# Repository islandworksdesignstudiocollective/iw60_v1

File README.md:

iw60_v1

****************************************************************************************

i was not impressed by the features, availability or price of other gh60 pcbs with o-ring compat so i made this

****************************************************************************************

-gh60 tray mount points

-all the baka nekos o-ring cutouts on edgecuts (afaik)

-alps+mx footprints

-onboad usb c, esd, h60 jst location yada yada

-routed to use no gnd plane cuz why not (a 2-sided fill zone has been drawn with isolation for the usb-c receptacle already, so you can choose to fill or remove it before making production files)

-duplex matrix cuz why not

-gondo reset circuit cuz why not

-bottom row is tsangan and 87u (so 7u wk/wkl or true hhkb or 87u wk with the 2 1us, as well as split space 3u) 

-does NOT support full right shift or ANSI bottom row 

-has accurately placed usb-c receptacle for gh60 standard. it is not lazily offset like most of the others i have seen, therefore i cannot confirm whether this will be well aligned with whatever pre-existing case that used a different gh60 compat pcb's 3d model to make their usb cutout

****************************************************************************************

as of right now, stm32g0b1cbt6 (and other stm mcus) seem to be in short supply, and other designers have reported issues with this mcu and qmk, so i have shelved this design. for that reason **this design has NOT been prototyped**. i don't have the energy right now to do a bom i will probably regret this in the future

the step file looks good to me. new versions of kicad are annoying to get the right thickness and export all the holes/components etc so if somethings missing its because i didn't notice :)

if you would like files for the same pcb with a different mcu you can check out iw60_v2 whenever i finish and publish that

****************************************************************************************

this is licensed under the Creative Commons Attribution Share-Alike 4.0 license, for the license's exact terms, see the LICENSE.md file

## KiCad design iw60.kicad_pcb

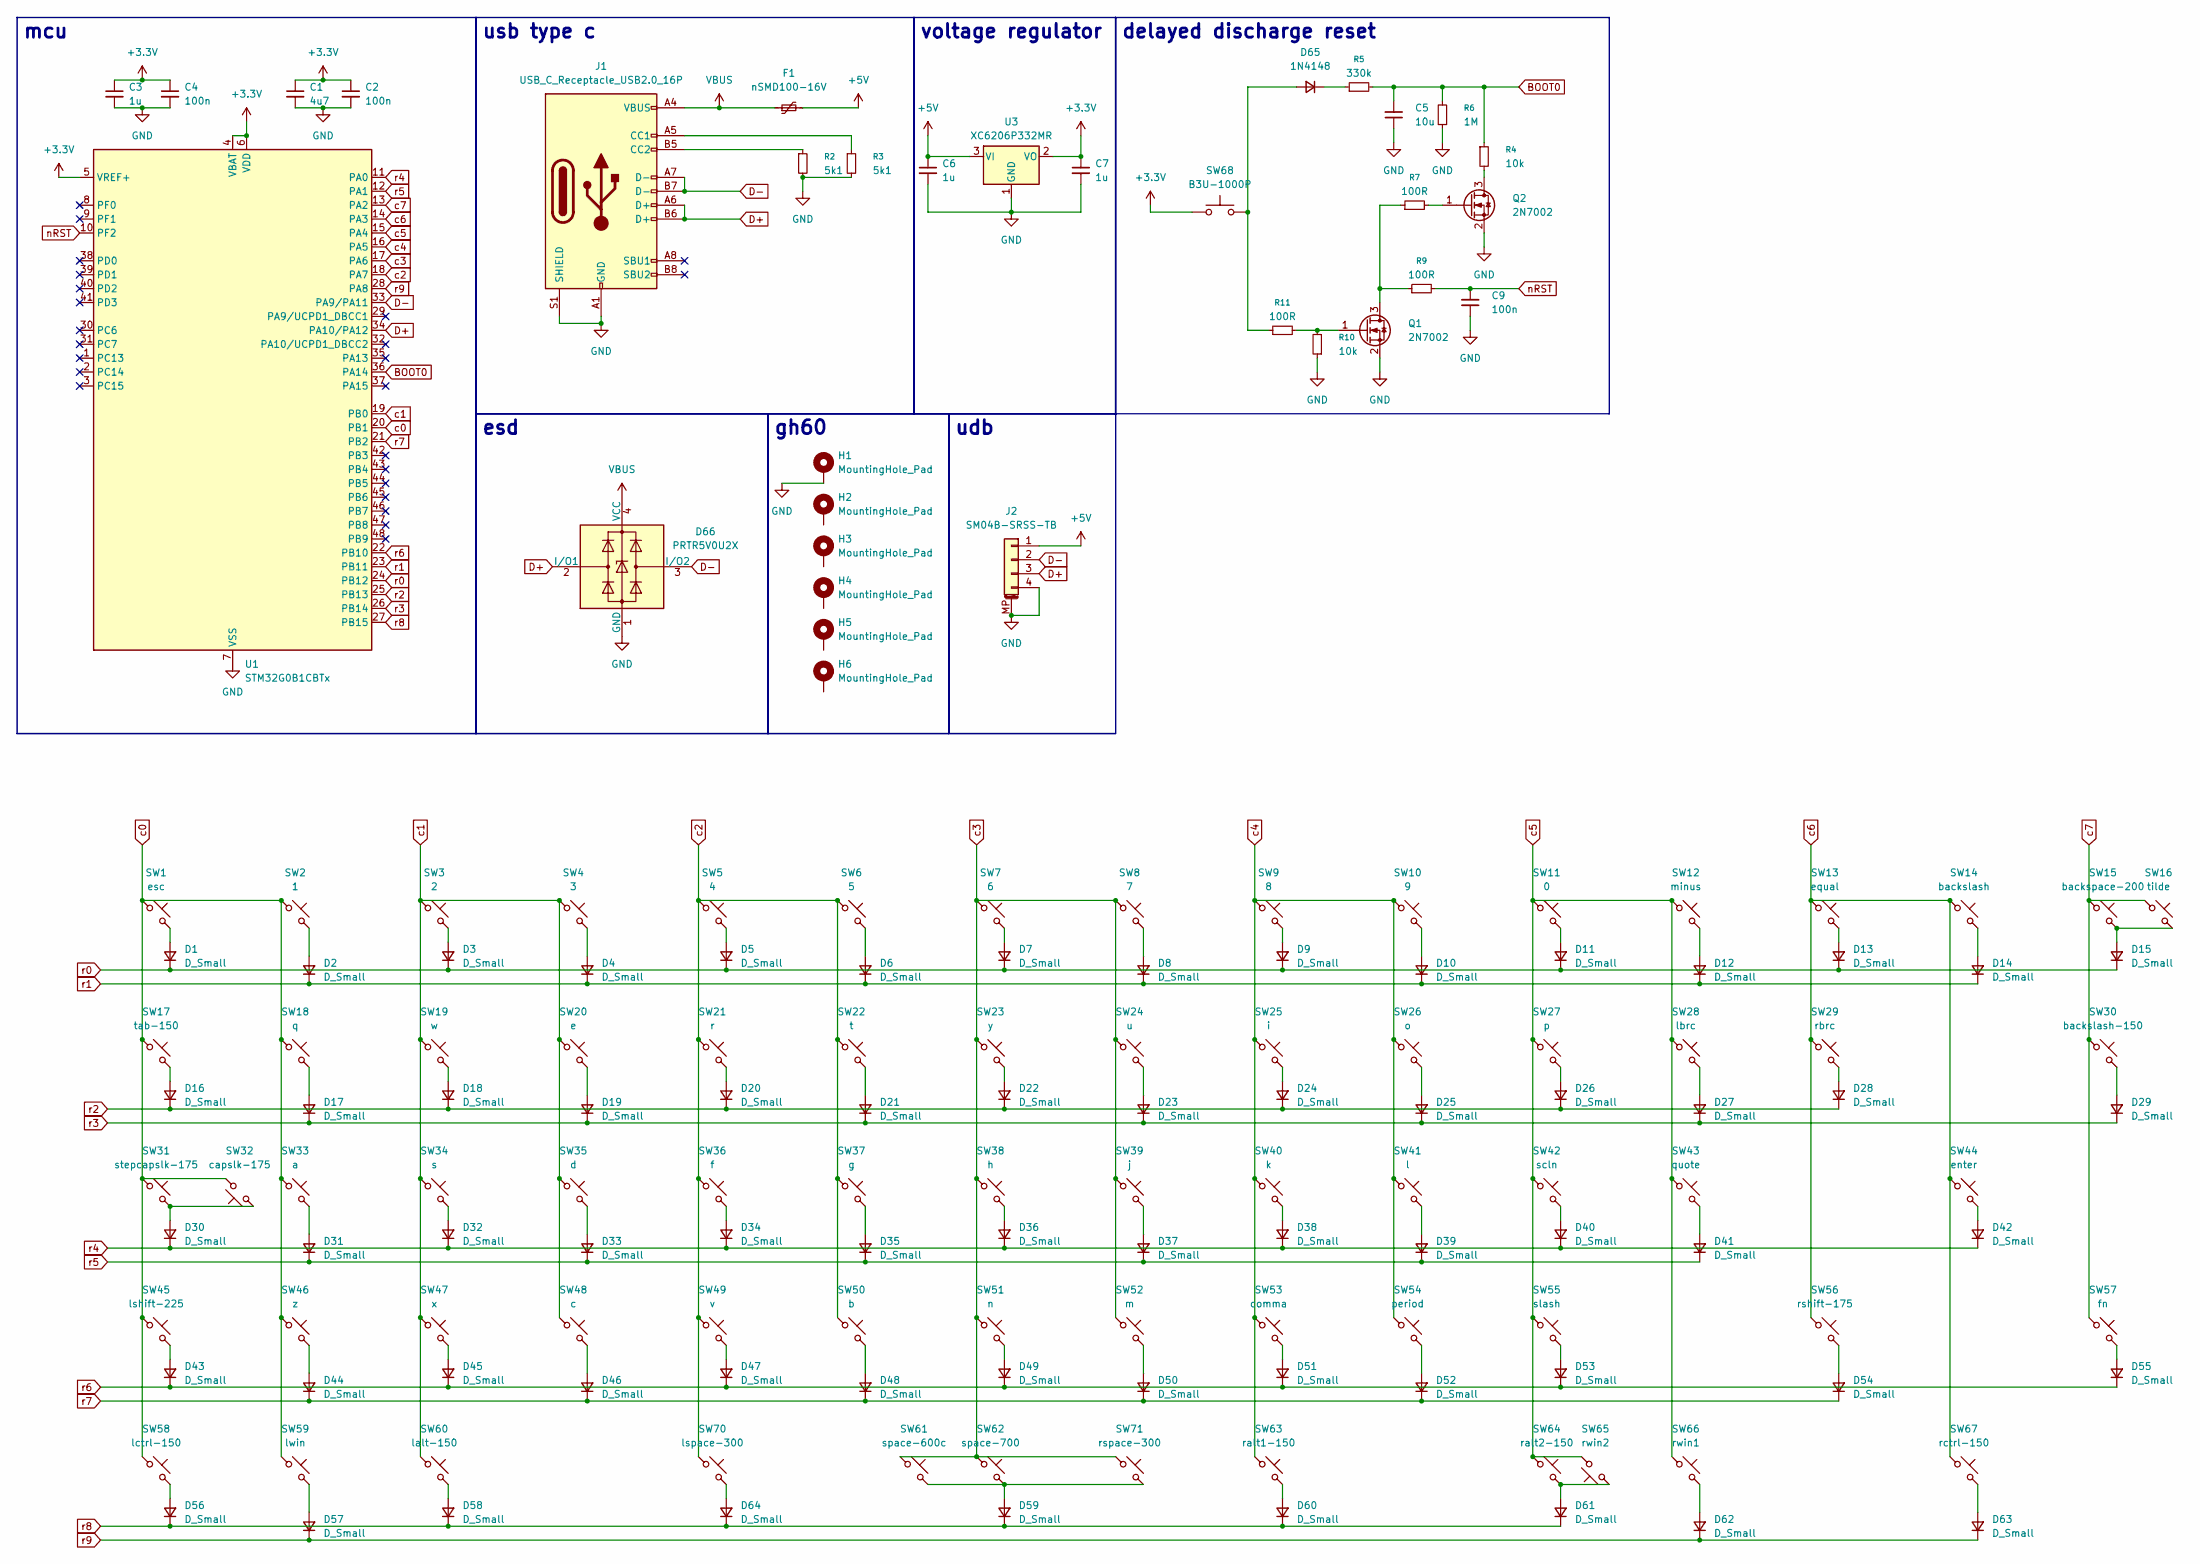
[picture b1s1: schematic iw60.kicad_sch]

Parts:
C1: 4u7; C_0402_1005Metric
C2, C4, C9: 100n; C_0402_1005Metric
C3, C6, C7: 1u; C_0402_1005Metric
C5: 10u; C_0402_1005Metric
D1, D2, D3, D4, D5, D6, D7, D8, D9, D10, D11, D12, D13, D14, D15, D16, D17, D18, D19, D20, D21, D22, D23, D24, D25, D26, D27, D28, D29, D30, D31, D32, D33, D34, D35, D36, D37, D38, D39, D40, D41, D42, D43, D44, D45, D46, D47, D48, D49, D50, D51, D52, D53, D54, D55, D56, D57, D58, D59, D60, D61, D62, D63, D64: D_Small; D_SOD-123
D65: 1N4148; D_SOD-123
D66: PRTR5V0U2X; SOT-143
F1: nSMD100-16V; Fuse_1206_3216Metric
H1: MountingHole_Pad; MountingHole_2.5mm_Pad_Via
H2, H3, H6: MountingHole_Pad; 5.5_5x2.5mm
H4, H5: MountingHole_Pad; 10x5_7x2.5mm
J1: USB_C_Receptacle_USB2.0_16P; USB_C_Receptacle_HRO_TYPE-C-31-M-12
J2: SM04B-SRSS-TB; JST_SH_SM04B-SRSS-TB_1x04-1MP_P1.00mm_Horizontal
Q1, Q2: 2N7002; SOT-23
R2, R3: 5k1; R_0402_1005Metric
R4, R10: 10k; R_0402_1005Metric
R5: 330k; R_0402_1005Metric
R6: 1M; R_0402_1005Metric
R7, R9, R11: 100R; R_0402_1005Metric
SW1: esc; MX-Alps-Hybrid-1U
SW2: 1; MX-Alps-Hybrid-1U-iw60-SW2
SW3: 2; MX-Alps-Hybrid-1U
SW4: 3; MX-Alps-Hybrid-1U
SW5: 4; MX-Alps-Hybrid-1U
SW6: 5; MX-Alps-Hybrid-1U
SW7: 6; MX-Alps-Hybrid-1U
SW8: 7; MX-Alps-Hybrid-1U
SW9: 8; MX-Alps-Hybrid-1U
SW10: 9; MX-Alps-Hybrid-1U
SW11: 0; MX-Alps-Hybrid-1U
SW12: minus; MX-Alps-Hybrid-1U
SW13: equal; MX-Alps-Hybrid-1U
SW14: backslash; MX-Alps-Hybrid-1U
SW15: backspace-200; MX-Alps-Hybrid-2U
SW16: tilde; MX-Alps-Hybrid-1U
SW17: tab-150; MX-Alps-Hybrid-1.5U
SW18: q; MX-Alps-Hybrid-1U
SW19: w; MX-Alps-Hybrid-1U
SW20: e; MX-Alps-Hybrid-1U
SW21: r; MX-Alps-Hybrid-1U
SW22: t; MX-Alps-Hybrid-1U
SW23: y; MX-Alps-Hybrid-1U
SW24: u; MX-Alps-Hybrid-1U
SW25: i; MX-Alps-Hybrid-1U
SW26: o; MX-Alps-Hybrid-1U
SW27: p; MX-Alps-Hybrid-1U
SW28: lbrc; MX-Alps-Hybrid-1U
SW29: rbrc; MX-Alps-Hybrid-1U
SW30: backslash-150; MX-Alps-Hybrid-1.5U
SW31: stepcapslk-175; MX-Alps-Hybrid-1.25U
SW32: capslk-175; MX-Alps-Hybrid-1.75U
SW33: a; MX-Alps-Hybrid-1U
SW34: s; MX-Alps-Hybrid-1U
SW35: d; MX-Alps-Hybrid-1U
SW36: f; MX-Alps-Hybrid-1U
SW37: g; MX-Alps-Hybrid-1U
SW38: h; MX-Alps-Hybrid-1U
SW39: j; MX-Alps-Hybrid-1U
SW40: k; MX-Alps-Hybrid-1U
SW41: l; MX-Alps-Hybrid-1U
SW42: scln; MX-Alps-Hybrid-1U
SW43: quote; MX-Alps-Hybrid-1U
SW44: enter; MX-Alps-Hybrid-2.25U
SW45: lshift-225; MX-Alps-Hybrid-2.25U
SW46: z; MX-Alps-Hybrid-1U
SW47: x; MX-Alps-Hybrid-1U
SW48: c; MX-Alps-Hybrid-1U
SW49: v; MX-Alps-Hybrid-1U
SW50: b; MX-Alps-Hybrid-1U
SW51: n; MX-Alps-Hybrid-1U
SW52: m; MX-Alps-Hybrid-1U
SW53: comma; MX-Alps-Hybrid-1U
SW54: period; MX-Alps-Hybrid-1U
SW55: slash; MX-Alps-Hybrid-1U
SW56: rshift-175; MX-Alps-Hybrid-1.75U
SW57: fn; MX-Alps-Hybrid-1U
SW58: lctrl-150; MX-Alps-Hybrid-1.5U
SW59: lwin; MX-Alps-Hybrid-1U
SW60: lalt-150; MX-Alps-Hybrid-1.5U
SW61: space-600c; MX-Alps-Hybrid-6U-ReversedStabilizers
SW62: space-700; MX-Alps-Hybrid-7U-ReversedStabilizers
SW63: ralt1-150; MX-Alps-Hybrid-1.5U
SW64: ralt2-150; MX-Alps-Hybrid-1.5U
SW65: rwin2; MX-Alps-Hybrid-1U
SW66: rwin1; MX-Alps-Hybrid-1U
SW67: rctrl-150; MX-Alps-Hybrid-1.5U
SW68: B3U-1000P; SW_SPST_B3U-1000P
SW70: lspace-300; MX-Alps-Hybrid-3U-ReversedStabilizers
SW71: rspace-300; MX-Alps-Hybrid-3U-ReversedStabilizers
U1: STM32G0B1CBTx; LQFP-48_7x7mm_P0.5mm
U3: XC6206P332MR; SOT-23-3

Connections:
+3.3V: C1.1, C2.1, C3.1, C4.1, C7.1, SW68.1, U1.4 (VBAT), U1.5 (VREF+), U1.6 (VDD), U3.2 (VO)
+5V: C6.1, F1.2, J2.1, U3.3 (VI)
BOOT0: C5.2, R4.1, R5.2, R6.2, U1.36 (PA14)
D+: D66.2 (I/O1), J1.A6 (D+), J1.B6 (D+), J2.3, U1.34 (PA10/PA12)
D-: D66.3 (I/O2), J1.A7 (D-), J1.B7 (D-), J2.2, U1.33 (PA9/PA11)
GND: C1.2, C2.2, C3.2, C4.2, C5.1, C6.2, C7.2, C9.1, D66.1 (GND), H1.1 (1_1), J1.A1 (GND), J1.A12 (GND), J1.B1 (GND), J1.B12 (GND), J1.S1 (SHIELD), J2.4, J2.MP (MountPin), Q1.2 (S), Q2.2 (S), R2.2, R3.2, R6.1, R10.1, U1.7 (VSS), U3.1 (GND)
unnamed: D1.2 (A), SW1.2
unnamed: D2.2 (A), SW2.2
unnamed: D3.2 (A), SW3.2
unnamed: D4.2 (A), SW4.2
unnamed: D5.2 (A), SW5.2
unnamed: D6.2 (A), SW6.2
unnamed: D7.2 (A), SW7.2
unnamed: D8.2 (A), SW8.2
unnamed: D9.2 (A), SW9.2
unnamed: D10.2 (A), SW10.2
unnamed: D11.2 (A), SW11.2
unnamed: D12.2 (A), SW12.2
unnamed: D13.2 (A), SW13.2
unnamed: D14.2 (A), SW14.2
unnamed: D15.2 (A), SW15.2, SW16.2
unnamed: D16.2 (A), SW17.2
unnamed: D17.2 (A), SW18.2
unnamed: D18.2 (A), SW19.2
unnamed: D19.2 (A), SW20.2
unnamed: D20.2 (A), SW21.2
unnamed: D21.2 (A), SW22.2
unnamed: D22.2 (A), SW23.2
unnamed: D23.2 (A), SW24.2
unnamed: D24.2 (A), SW25.2
unnamed: D25.2 (A), SW26.2
unnamed: D26.2 (A), SW27.2
unnamed: D27.2 (A), SW28.2
unnamed: D28.2 (A), SW29.2
unnamed: D29.2 (A), SW30.2
unnamed: D30.2 (A), SW31.2, SW32.1
unnamed: D31.2 (A), SW33.2
unnamed: D32.2 (A), SW34.2
unnamed: D33.2 (A), SW35.2
unnamed: D34.2 (A), SW36.2
unnamed: D35.2 (A), SW37.2
unnamed: D36.2 (A), SW38.2
unnamed: D37.2 (A), SW39.2
unnamed: D38.2 (A), SW40.2
unnamed: D39.2 (A), SW41.2
unnamed: D40.2 (A), SW42.2
unnamed: D41.2 (A), SW43.2
unnamed: D42.2 (A), SW44.2
unnamed: D43.2 (A), SW45.2
unnamed: D44.2 (A), SW46.2
unnamed: D45.2 (A), SW47.2
unnamed: D46.2 (A), SW48.2
unnamed: D47.2 (A), SW49.2
unnamed: D48.2 (A), SW50.2
unnamed: D49.2 (A), SW51.2
unnamed: D50.2 (A), SW52.2
unnamed: D51.2 (A), SW53.2
unnamed: D52.2 (A), SW54.2
unnamed: D53.2 (A), SW55.2
unnamed: D54.2 (A), SW56.2
unnamed: D55.2 (A), SW57.2
unnamed: D56.2 (A), SW58.2
unnamed: D57.2 (A), SW59.2
unnamed: D58.2 (A), SW60.2
unnamed: D59.2 (A), SW61.2, SW62.2, SW71.2
unnamed: D60.2 (A), SW63.2
unnamed: D61.2 (A), SW64.2, SW65.1
unnamed: D62.2 (A), SW66.2
unnamed: D63.2 (A), SW67.2
unnamed: D64.2 (A), SW70.2
unnamed: D65.2 (A), R11.1, SW68.2
unnamed: D65.1 (K), R5.1
unnamed: J1.A5 (CC1), R3.1
unnamed: J1.B5 (CC2), R2.1
unnamed: Q1.3 (D), R7.1, R9.1
unnamed: Q1.1 (G), R10.2, R11.2
unnamed: Q2.3 (D), R4.2
unnamed: Q2.1 (G), R7.2
VBUS: D66.4 (VCC), F1.1, J1.A4 (VBUS), J1.A9 (VBUS), J1.B4 (VBUS), J1.B9 (VBUS)
c0: SW1.1, SW2.1, SW17.1, SW18.1, SW31.1, SW32.2, SW33.1, SW45.1, SW46.1, SW58.1, SW59.1, U1.20 (PB1)
c1: SW3.1, SW4.1, SW19.1, SW20.1, SW34.1, SW35.1, SW47.1, SW48.1, SW60.1, U1.19 (PB0)
c2: SW5.1, SW6.1, SW21.1, SW22.1, SW36.1, SW37.1, SW49.1, SW50.1, SW70.1, U1.18 (PA7)
c3: SW7.1, SW8.1, SW23.1, SW24.1, SW38.1, SW39.1, SW51.1, SW52.1, SW61.1, SW62.1, SW71.1, U1.17 (PA6)
c4: SW9.1, SW10.1, SW25.1, SW26.1, SW40.1, SW41.1, SW53.1, SW54.1, SW63.1, U1.16 (PA5)
c5: SW11.1, SW12.1, SW27.1, SW28.1, SW42.1, SW43.1, SW55.1, SW64.1, SW65.2, SW66.1, U1.15 (PA4)
c6: SW13.1, SW14.1, SW29.1, SW44.1, SW56.1, SW67.1, U1.14 (PA3)
c7: SW15.1, SW16.1, SW30.1, SW57.1, U1.13 (PA2)
nRST: C9.2, R9.2, U1.10 (PF2)
r0: D1.1 (K), D3.1 (K), D5.1 (K), D7.1 (K), D9.1 (K), D11.1 (K), D13.1 (K), D15.1 (K), U1.24 (PB12)
r1: D2.1 (K), D4.1 (K), D6.1 (K), D8.1 (K), D10.1 (K), D12.1 (K), D14.1 (K), U1.23 (PB11)
r2: D16.1 (K), D18.1 (K), D20.1 (K), D22.1 (K), D24.1 (K), D26.1 (K), D28.1 (K), U1.25 (PB13)
r3: D17.1 (K), D19.1 (K), D21.1 (K), D23.1 (K), D25.1 (K), D27.1 (K), D29.1 (K), U1.26 (PB14)
r4: D30.1 (K), D32.1 (K), D34.1 (K), D36.1 (K), D38.1 (K), D40.1 (K), D42.1 (K), U1.11 (PA0)
r5: D31.1 (K), D33.1 (K), D35.1 (K), D37.1 (K), D39.1 (K), D41.1 (K), U1.12 (PA1)
r6: D43.1 (K), D45.1 (K), D47.1 (K), D49.1 (K), D51.1 (K), D53.1 (K), D55.1 (K), U1.22 (PB10)
r7: D44.1 (K), D46.1 (K), D48.1 (K), D50.1 (K), D52.1 (K), D54.1 (K), U1.21 (PB2)
r8: D56.1 (K), D58.1 (K), D59.1 (K), D60.1 (K), D61.1 (K), D64.1 (K), U1.27 (PB15)
r9: D57.1 (K), D62.1 (K), D63.1 (K), U1.28 (PA8)

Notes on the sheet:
esd
mcu
delayed discharge reset
usb type c
voltage regulator
gh60
udb

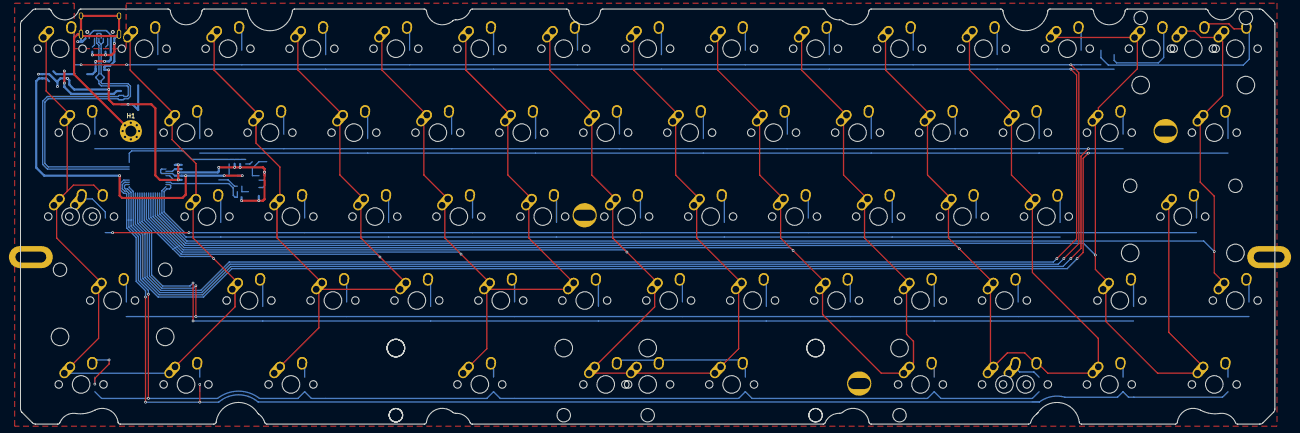
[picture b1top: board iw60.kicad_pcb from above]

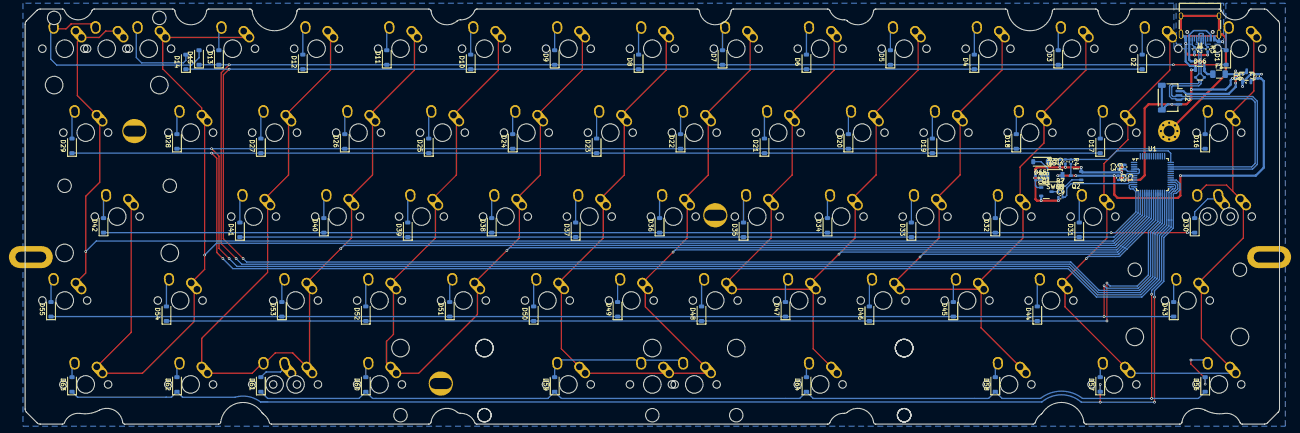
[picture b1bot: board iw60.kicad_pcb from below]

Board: 2 copper layers, 284.7 x 94.2 mm, 166 parts (91 on the bottom side), 98 nets.
